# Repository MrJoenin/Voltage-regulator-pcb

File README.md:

# Adjustable Linear Power Supply Using LM338

This project is a high-current adjustable linear voltage regulator based on the LM338. The design provides a stable and adjustable DC output suitable for electronics prototyping, robotics, and general lab use. A custom PCB was designed in KiCad, making the circuit compact, reliable, and easy to reproduce.

The LM338 is capable of supplying up to 5 A of output current, making this regulator suitable for powering microcontrollers, sensors, small motors, and other moderate-current loads.

## Features
- Adjustable output voltage from 1.2 V up to 32 V
- Input voltage range up to 35 V DC
- Output current up to 5 A (with proper heat sinking)
- Linear regulation for low noise and stable output
- Protection diodes to prevent regulator damage during:
  - Output short circuits
  - Large output capacitor discharge
- Screw terminals for easy power input and output
- Custom PCB designed using KiCad

## Circuit Overview
The output voltage is set using a resistor and potentiometer connected to the ADJ pin of the LM338. The relationship between the resistors determines the regulated output voltage.
Two protection diodes are included:
- One diode between Vout and Vin to protect the LM338 if the input is shorted
- One diode between Vout and ADJ to prevent reverse current through the adjustment pin

Input and output capacitors are used to improve stability and transient response.

## Applications
- Bench power supply
- Robotics projects
- Arduino and microcontroller power source
- Analog and digital circuit testing
- Educational use for learning linear regulators and PCB design

## Design Tools
- Schematic & PCB: KiCad
- Regulator IC: LM338
- PCB: Single-board linear regulator design

## Notes

- A heat sink is required when operating at high current or large input–output voltage differences.
- This is a linear regulator, so power dissipation increases with higher current and voltage drop.
- Reverse polarity protection can be added externally or in future PCB revisions.

# Block Diagram Description
## Block Flow:

DC Input → Protection → LM338 Regulator → Output Filter → Adjustable DC Output

## Block Explanation
1. DC Input
    - Power is supplied through a screw terminal connector.
    - Accepts a DC input voltage up to 35 V.

2. Protection Network
    - Protection diodes prevent reverse current flow through the LM338 during:
      - Input short circuits
      - Output capacitor discharge
    - This improves regulator reliability and longevity.

3. LM338 Adjustable Regulator
    - The LM338 regulates the input voltage and provides up to 5 A of output current.
    - Output voltage is set using a fixed resistor and a potentiometer connected to the ADJ pin.

4. Output Filtering
    - Output capacitors improve stability and transient response.
    - Reduces voltage ripple and noise at the load.

5. Adjustable DC Output
    - Regulated and adjustable output voltage available at the output screw terminal.
    - Suitable for powering a wide range of electronic circuits and subsystems.

# Future Improvements

- Reverse Polarity Protection
  - Add a P-channel MOSFET–based reverse polarity protection circuit at the input to prevent damage if the power supply is connected backward.
  - This would eliminate voltage drop compared to a series diode solution.

- Current Limiting / Protection
  - Add external current sensing or foldback current limiting to better protect the load and regulator under fault conditions.

- Thermal Protection Enhancements
  - Include PCB-mounted temperature sensing or thermal cutoff circuitry.
  - Improve copper pours and thermal vias for better heat dissipation.

- Digital Voltage Monitoring
  - Add a voltmeter or ADC interface to display or measure output voltage digitally.
  - Useful for bench power supply applications.

- Improved PCB Layout
  - Widen high-current traces.
  - Optimize ground planes and star grounding to reduce noise and voltage drop.

- Enclosure & User Interface
  - Design a 3D-printable enclosure.
  - Add labeling, test points, and optional power indicator LEDs.

- Multiple Output Versions
  - Expand the design to support multiple regulated outputs or selectable voltage rails.

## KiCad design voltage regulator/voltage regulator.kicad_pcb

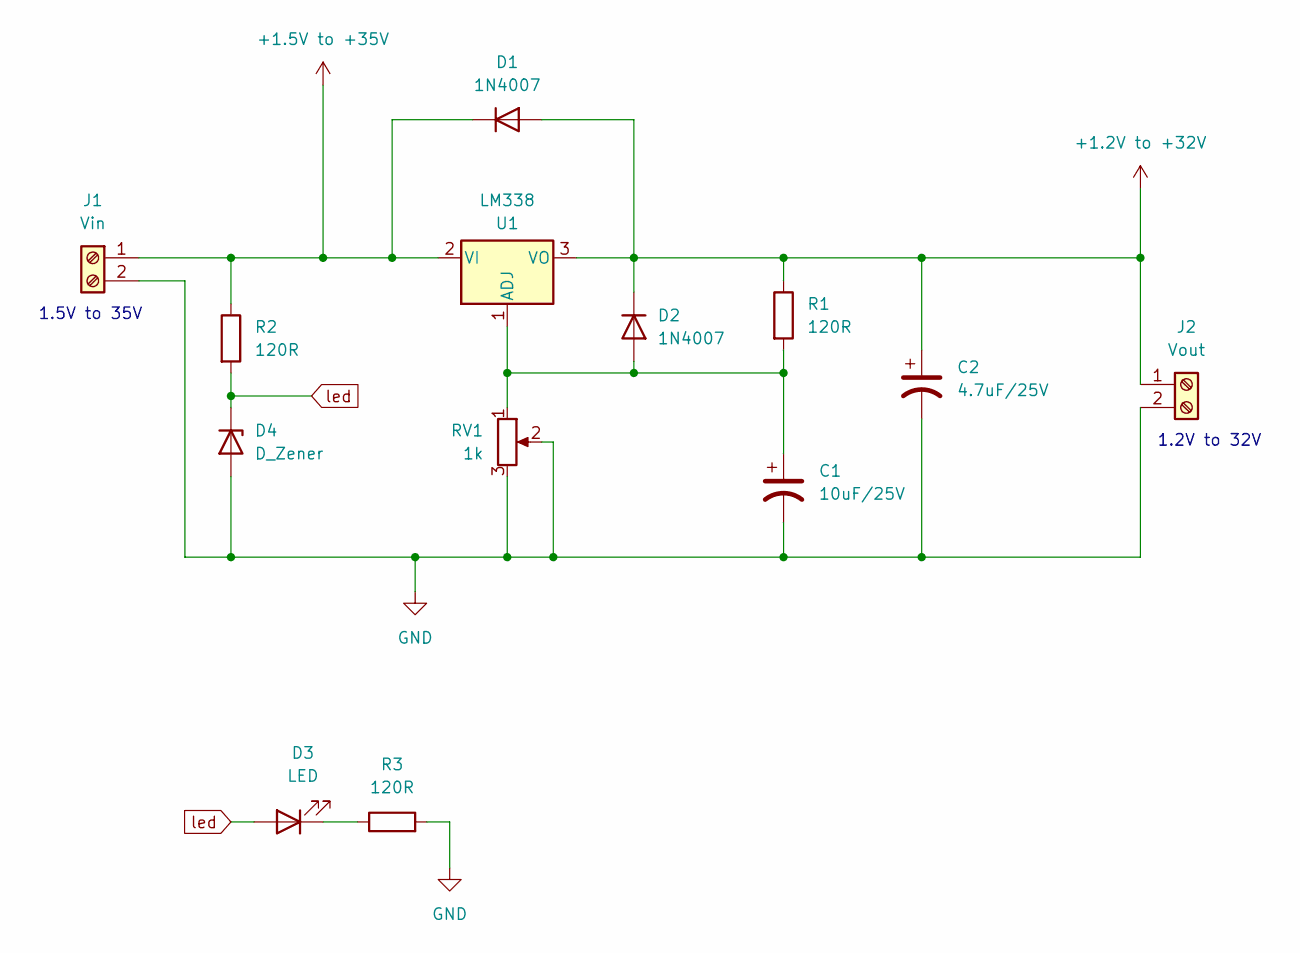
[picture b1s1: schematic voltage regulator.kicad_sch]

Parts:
C1: 10uF/25V; C_Radial_D4.0mm_H7.0mm_P1.50mm
C2: 4.7uF/25V; C_Radial_D5.0mm_H11.0mm_P2.00mm
D1, D2: 1N4007; D_DO-41_SOD81_P10.16mm_Horizontal
D3: LED; LED_1206_3216Metric
D4: D_Zener; D_0805_2012Metric_Pad1.15x1.40mm_HandSolder
J1: Vin; TerminalBlock_Phoenix_MKDS-1,5-2-5.08_1x02_P5.08mm_Horizont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
J2: Vout; TerminalBlock_Phoenix_MKDS-1,5-2-5.08_1x02_P5.08mm_Horizont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
R1, R2, R3: 120R; R_1206_3216Metric_Pad1.30x1.75mm_HandSolder
RV1: 1k; Potentiometer_Bourns_3266W_Vertical
U1: LM338; SOT-223-3_TabPin2

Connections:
+1.2V to +32V: C2.1, D1.2 (A), D2.1 (K), J2.1, R1.1, U1.3 (VO); also elsewhere on the board
+1.5V to +35V: D1.1 (K), J1.1, R2.1, U1.2 (VI)
GND: C1.2, C2.2, D4.2 (A), J1.2, J2.2, R3.2, RV1.2, RV1.3; also elsewhere on the board
unnamed: C1.1, D2.2 (A), R1.2, RV1.1, U1.1 (ADJ)
unnamed: D3.1 (K), R3.1
led: D3.2 (A), D4.1 (K), R2.2

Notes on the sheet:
1.5V to 35V
1.2V to 32V

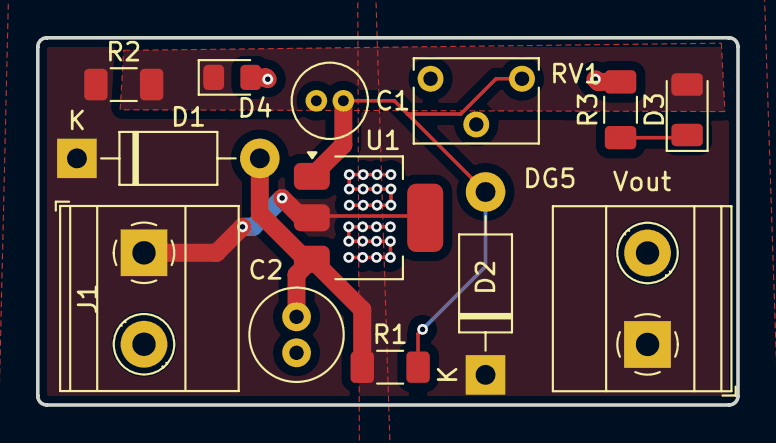
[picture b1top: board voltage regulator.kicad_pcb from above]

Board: 2 copper layers, 38.9 x 20.4 mm, 13 parts (0 on the bottom side), 6 nets.

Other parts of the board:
Vout: Vout; TerminalBlock_Phoenix_MKDS-1,5-2-5.08_1x02_P5.08mm_Horizont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

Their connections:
+1.2V to +32V: Vout.1; also elsewhere on the board
GND: Vout.2; also elsewhere on the board

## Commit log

2025-12-30 Revise Features section in README.md
    Updated the Features section for clarity and formatting.
2025-12-30 Clean up features list in README
    Removed redundant bullet points from the features list.
2025-12-30 Correct bullet point formatting in README
    Fix formatting of bullet points in the README.
2025-12-30 Refactor Circuit Overview section in README.md
    Corrected formatting and removed redundant lines in the Circuit Overview section.
2025-12-30 Consolidate notes in README.md
2025-12-30 Update README formatting and section headers
2025-12-30 Clean up Block Explanation in README.md
    Removed redundant lines from the Block Explanation section.
2025-12-30 Fix formatting and numbering in Block Explanation section
    Corrected the numbering and formatting of the block explanation in the README.
2025-12-30 Refine formatting in Block Explanation of README
    Removed extra bullet points for clarity in the Block Explanation section.
2025-12-30 Refine protection network section in README
    Removed redundant points about input short circuits and output capacitor discharge for clarity.
2025-12-30 Update LM338 Adjustable Regulator section in README
    Reorganize LM338 section and improve formatting.
2025-12-30 Refactor README for improved clarity and structure
    Reorganized and improved the layout of the README sections for clarity.
